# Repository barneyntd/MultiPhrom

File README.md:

Multiphrom
==========

Multiphrom is a small microcontroller based board designed to emulate serial speech ROMS (phroms) for the BBC microcomputer.
It differs from many similar devices in several ways:
1.  Rather than emulating just one phrom, Multiphrom emulates up to 64;
2.  The contents of the emulated phroms can be updated at any time by inserting a micro-SD card;
3.  Multiphrom attempts to detect other phroms and stops using contended addresses;
4.  Multiphrom plugs into the official cartridge slot in the keyboard (the ashtray), or onto the external rom connector, PL14.

#### Project folders
- **kicad** This holds the schematic and pcb design, as a kicad project;
- **src** This holds the source code, written in C, and a Makefile to build it;
- **docs** This holds documents explaining how to use multiphrom, and the BBC micro speech system;
- **BASIC** This holds several sample programs, written in BBC BASIC.
- **Phroms** This holds some sample phroms for testing.

#### Licence
This project is licensed under creative commons licence [CC BY-NC-SA 4.0](https://creativecommons.org/licenses/by-nc-sa/4.0/).
This means that you are free to use it for any noncommercial purpose, provided you credit the copyright holder, and pass on the same conditions.
If you want to create a commercial product based on Multiphrom, you must obtain a seperate licence from the copyright holder.

The project includes the [sd-reader](http://www.roland-riegel.de/sd-reader/index.html) library by Roland Riegel, which is licenced under GNU LGPL v2.1.

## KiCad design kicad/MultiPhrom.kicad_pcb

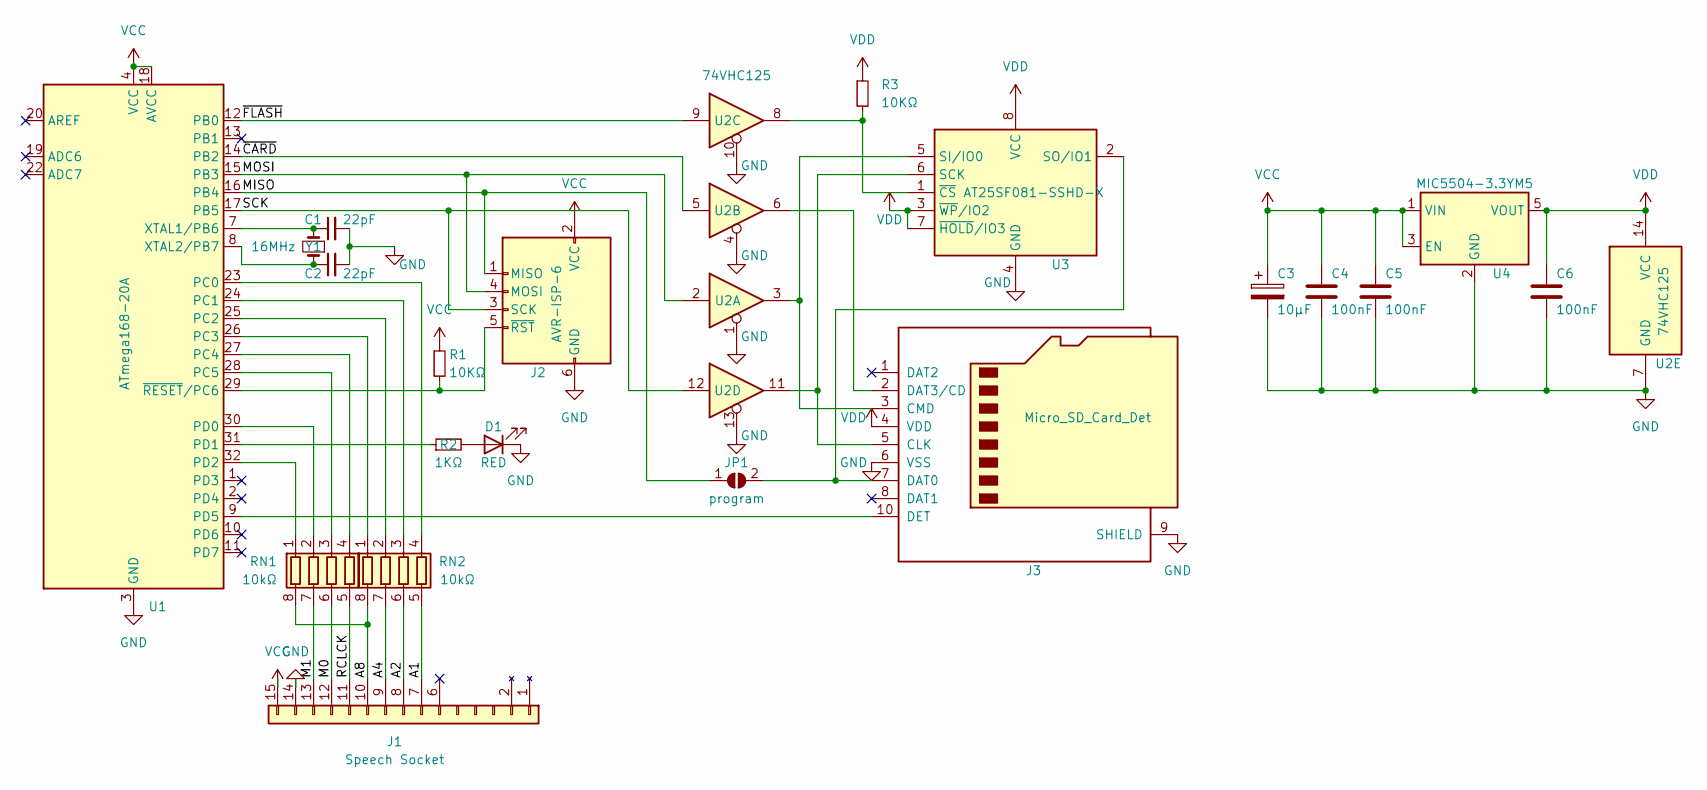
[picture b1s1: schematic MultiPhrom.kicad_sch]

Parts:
C1, C2: 22pF; C_1206_3216Metric_Pad1.33x1.80mm_HandSolder
C3: 10µF; CP_Radial_D5.0mm_P2.00mm
C4, C5, C6: 100nF; C_1206_3216Metric_Pad1.33x1.80mm_HandSolder
D1: RED; LED_1206_3216Metric_Pad1.42x1.75mm_HandSolder
J1: Speech Socket; BBC Speech Socket
J2: AVR-ISP-6; PinHeader_2x03_P2.54mm_Vertical
J3: Micro_SD_Card_Det; WR-CRD 693071010811
JP1: program; SolderJumper-2_P1.3mm_Open_RoundedPad1.0x1.5mm
R1, R3: 10KΩ; R_1206_3216Metric_Pad1.30x1.75mm_HandSolder
R2: 1KΩ; R_1206_3216Metric_Pad1.30x1.75mm_HandSolder
RN1, RN2: 10kΩ; R_Array_Convex_4x1206
U1: ATmega168-20A; TQFP-32_7x7mm_P0.8mm
U2: 74VHC125; SO-14_3.9x8.65mm_P1.27mm
U3: AT25SF081-SSHD-X; SOIC-8_3.9x4.9mm_P1.27mm
U4: MIC5504-3.3YM5; SOT-23-5
Y1: 16MHz; Crystal_HC49-4H_Vertical

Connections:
/A1: J1.7, RN2.5 (R4.2)
/A2: J1.8, RN2.6 (R3.2)
/A4: J1.9, RN2.7 (R2.2)
/A8: J1.10, RN1.8 (R1.2), RN2.8 (R1.2)
/M0: J1.12, RN1.6 (R3.2)
/M1: J1.13, RN1.7 (R2.2)
/MISO: J2.1 (MISO), JP1.1 (A), U1.16 (PB4)
/MOSI: J2.4 (MOSI), U1.15 (PB3), U2.2
/RCLCK: J1.11, RN1.5 (R4.2)
/SCK: J2.3 (SCK), U1.17 (PB5), U2.12
/~CARD: U1.14 (PB2), U2.5
/~FLASH: U1.12 (PB0), U2.9
GND: C1.2, C2.2, C3.2, C4.2, C5.2, C6.2, D1.1 (K), J1.14, J2.6 (GND), J3.6 (VSS), J3.9 (SHIELD), U1.3 (GND), U1.5 (GND), U1.21 (GND), U2.1, U2.4, U2.7 (GND), U2.10, U2.13, U3.4 (GND), U4.2 (GND)
unnamed: C1.1, U1.7 (XTAL1/PB6), Y1.2
unnamed: C2.1, U1.8 (XTAL2/PB7), Y1.1
unnamed: D1.2 (A), R2.2
unnamed: J2.5 (~RST), R1.2, U1.29 (~RESET/PC6)
unnamed: J3.2 (DAT3/CD), U2.6
unnamed: J3.3 (CMD), U2.3, U3.5 (SI/IO0)
unnamed: J3.5 (CLK), U2.11, U3.6 (SCK)
unnamed: J3.7 (DAT0), JP1.2 (B), U3.2 (SO/IO1)
unnamed: J3.10 (DET), U1.9 (PD5)
unnamed: R2.1, U1.31 (PD1)
unnamed: R3.2, U2.8, U3.1 (~CS)
unnamed: RN1.1 (R1.1), U1.32 (PD2)
unnamed: RN1.2 (R2.1), U1.30 (PD0)
unnamed: RN1.3 (R3.1), U1.28 (PC5)
unnamed: RN1.4 (R4.1), U1.27 (PC4)
unnamed: RN2.1 (R1.1), U1.26 (PC3)
unnamed: RN2.2 (R2.1), U1.25 (PC2)
unnamed: RN2.3 (R3.1), U1.24 (PC1)
unnamed: RN2.4 (R4.1), U1.23 (PC0)
VCC: C3.1, C4.1, C5.1, J1.15, J2.2 (VCC), R1.1, U1.4 (VCC), U1.6 (VCC), U1.18 (AVCC), U4.1 (VIN), U4.3 (EN)
VDD: C6.1, J3.4 (VDD), R3.1, U2.14 (VCC), U3.3 (~WP/IO2), U3.7 (~HOLD/IO3), U3.8 (VCC), U4.5 (VOUT)

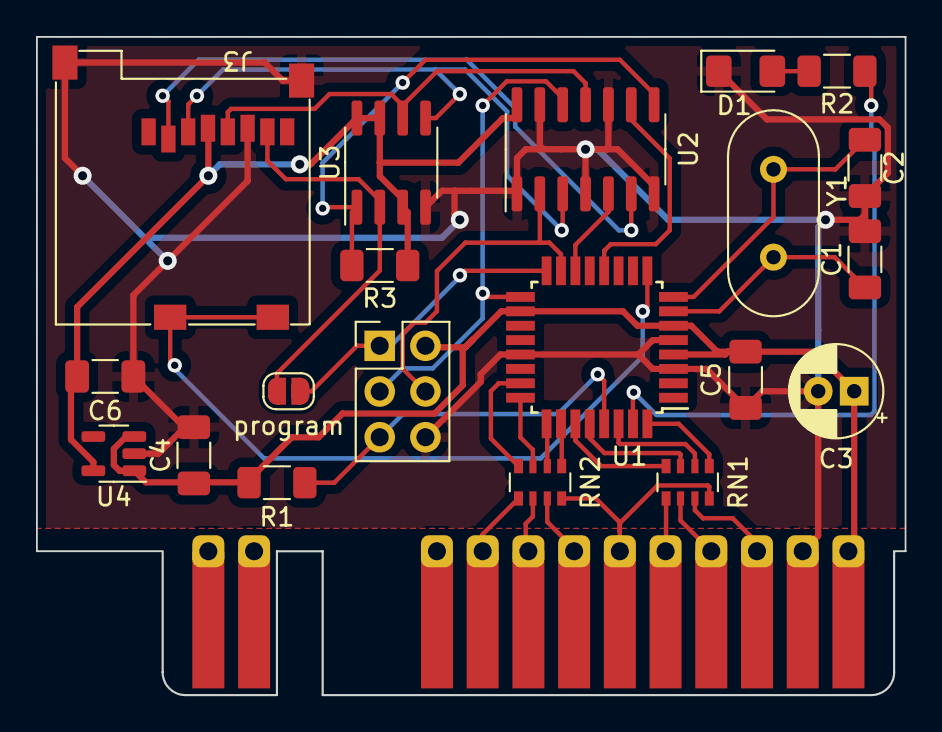
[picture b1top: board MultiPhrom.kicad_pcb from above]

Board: 2 copper layers, 48.2 x 36.6 mm, 21 parts (0 on the bottom side), 34 nets.

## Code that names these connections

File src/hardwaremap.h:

//
//  hardwaremap.h
//  MultiPhrom
//
//  Created by Barney Hilken on 20/03/2020.
//  Copyright © 2020 Barney Hilken. This file is free for noncommercial use: see licence for details.
//


#ifndef HARDWAREMAP_H_
#define HARDWAREMAP_H_

// Global includes
#include <avr/io.h>

// Some useful definitions
#define FALSE	0
#define TRUE	1
#define NULL    0


// TMS6100 IO Pins

// M0 (PC5)
#define M0_BITMASK          (1 << 5)
#define SET_M0_INPUT        DDRC &= ~M0_BITMASK
#define SET_M0_NOPULLUP     PORTC &= ~M0_BITMASK
#define M0                  ((PINC & M0_BITMASK) != 0)

// M1 (PD0)
#define M1_BITMASK          (1 << 0)
#define SET_M1_INPUT        DDRD &= ~M1_BITMASK
#define SET_M1_NOPULLUP     PORTD &= ~M1_BITMASK
#define M1                  ((PIND & M1_BITMASK) != 0)

// ROMCLK (PC4)
#define CLK_BITMASK         (1 << 4)
#define SET_CLK_INPUT       DDRC &= ~CLK_BITMASK
#define SET_CLK_NOPULLUP    PORTC &= ~CLK_BITMASK
#define CLK                 ((PINC & CLK_BITMASK) != 0)

// ADD (PC0-3)
#define ADD1_BIT            0
#define ADD_BITMASK         (0x0F << ADD1_BIT)
#define SET_ADD_INPUT       DDRC &= ~ADD_BITMASK
#define SET_ADD_NOPULLUP    PORTC &= ~ADD_BITMASK
#define ADD                 ((PINC & ADD_BITMASK) >> ADD1_BIT)

// ADD8 (ADD >> 3)
#define ADD8_BITMASK        (1 << (ADD1_BIT + 3))
#define ADD8                ((PINC & ADD8_BITMASK) != 0)

// DATA (PD2), connected to ADD8 via resistor
#define DATA_BITMASK        (1 << 2)
#define SET_DATA_INPUT      DDRD &= ~DATA_BITMASK
#define SET_DATA_OUTPUT     DDRD |= DATA_BITMASK
#define SET_DATA(b)         PORTD = (PORTD & ~DATA_BITMASK) | ((b) ? DATA_BITMASK : 0)

// SPI interface

// MISO (PB4)
#define MISO_BITMASK        (1 << 4)
#define SET_MISO_INPUT      DDRB &= ~MISO_BITMASK
#define SET_MISO_NOPULLUP   PORTB &= ~MISO_BITMASK
#define MISO                ((PINB & MISO_BITMASK) != 0)

// MOSI (PB3)
#define MOSI_BIT            3
#define MOSI_BITMASK        (1 << MOSI_BIT)
#define SET_MOSI_OUTPUT     DDRB |= MOSI_BITMASK
#define SET_MOSI(b)         PORTB = (PORTB & ~MOSI_BITMASK) | ((b) ? MOSI_BITMASK : 0)

// SCK (PB5)
#define SCK_BIT             5
#define SCK_BITMASK         (1 << SCK_BIT)
#define SET_SCK_OUTPUT      DDRB |= SCK_BITMASK
#define SET_SCK(b)          PORTB = (PORTB & ~SCK_BITMASK) | ((b) ? SCK_BITMASK : 0)

// CHIP (PB0)
#define CHIP_BIT            0
#define CHIP_BITMASK        (1 << CHIP_BIT)
#define SET_CHIP_OUTPUT     DDRB |= CHIP_BITMASK
#define SET_CHIP(b)         PORTB = (PORTB & ~CHIP_BITMASK) | ((b) ? CHIP_BITMASK : 0)

// CARD (PB2)
#define CARD_BIT            2
#define CARD_BITMASK        (1 << CARD_BIT)
#define SET_CARD_OUTPUT     DDRB |= CARD_BITMASK
#define SET_CARD(b)         PORTB = (PORTB & ~CARD_BITMASK) | ((b) ? CARD_BITMASK : 0)

// Other IO pins

// LED (PD1)
#define LED_BIT             1
#define LED_BITMASK         (1 << LED_BIT)
#define SET_LED_OUTPUT      DDRD |= LED_BITMASK
#define SET_LED(b)          PORTD = (PORTD & ~LED_BITMASK) | ((b) ? LED_BITMASK : 0)

// DTCT (PD5)
#define DTCT_BITMASK        (1 << 5)
#define SET_DTCT_INPUT      DDRD &= ~DTCT_BITMASK
#define SET_DTCT_PULLUP     PORTD |= DTCT_BITMASK
#define DTCT                ((PIND & DTCT_BITMASK) != 0)
#define DTCT_INT_vect       PCINT2_vect
#define DTCT_INT_enable     PCMSK2 |= (1 << PCINT21); PCICR |= (1 << PCIE2)



// turn off unused features
#define UNUSED_OFF          PRR = (1 << PRADC) | (1 << PRUSART0) | (1 << PRTIM1) | (1 << PRTIM0) | (1 << PRTIM2) | (1 << PRTWI)

#endif /* HARDWAREMAP_H_ */

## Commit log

2024-03-20 Initial git commit
2024-03-20 Create LICENSEhtml
2024-03-20 Create LICENSE
2024-03-20 remove Phrom folder
2024-03-22 Create README.md for src
2024-03-25 more examples
2024-04-14 Add sample phroms
